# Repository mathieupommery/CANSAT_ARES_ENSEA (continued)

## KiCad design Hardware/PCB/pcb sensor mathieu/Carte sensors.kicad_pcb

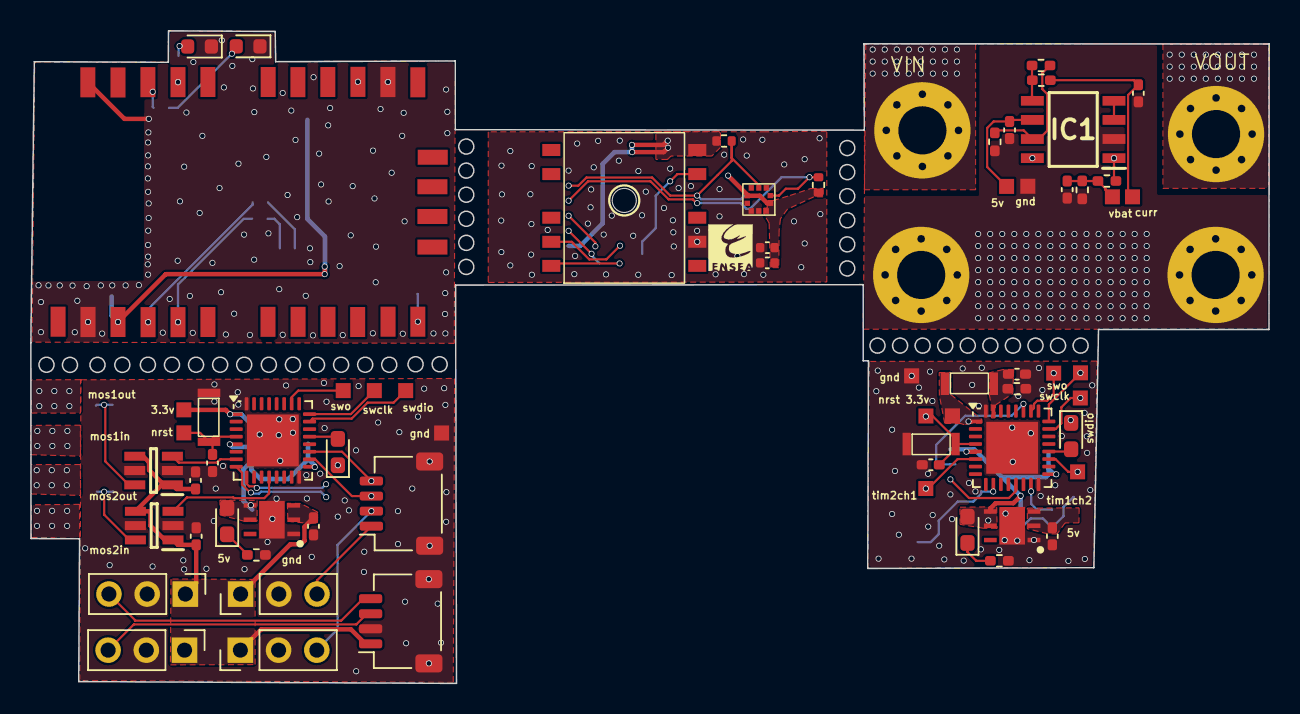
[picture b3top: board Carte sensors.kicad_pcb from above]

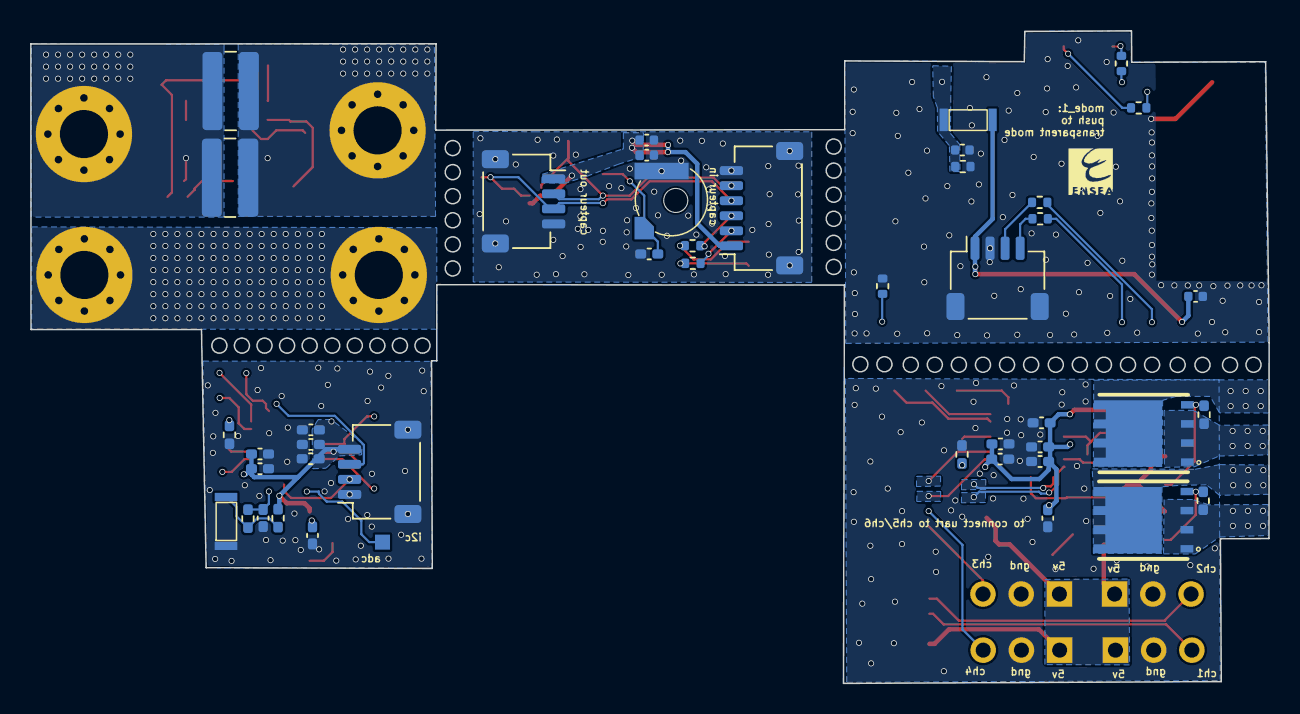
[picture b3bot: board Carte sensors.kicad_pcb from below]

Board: 2 copper layers, 82.3 x 43.4 mm, 94 parts (43 on the bottom side), 59 nets.

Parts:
BT1: ML414S; MS421R-IV03E
C1: 10n; C_0402_1005Metric
C2, C3, C4: 100u; C_0402_1005Metric
C5: 4.7u; C_0402_1005Metric
C6: 100n; C_0402_1005Metric
C7, C16, C19, C23, C29: 10n; C_0402_1005Metric_Pad0.74x0.62mm_HandSolder
C8, C10, C12, C17, C24, C25, C26, C27, C28, C30: 1u; C_0402_1005Metric_Pad0.74x0.62mm_HandSolder
C9, C14, C15, C21, C22: 100n; C_0402_1005Metric_Pad0.74x0.62mm_HandSolder
C11, C18: 0.1u; C_0402_1005Metric_Pad0.74x0.62mm_HandSolder
C13, C20: 4.7u; C_0402_1005Metric_Pad0.74x0.62mm_HandSolder
D1, D2: LED_Small; LED_0603_1608Metric
D3, D4, D5, D6: LED; LED_0603_1608Metric_Pad1.05x0.95mm_HandSolder
H1, H2, H3, H4: MountingHole_Pad; MountingHole_3.2mm_M3_Pad_Via
IC1: TSC102IDT; SOIC127P600X175-8N
IC2, IC3: LDO40LPU33RY; SON95P300X300X90-7N-D
IC4, IC5: MCP14A0151T-E_CH; SOT95P270X145-6N
J1, J3, J4, J5, J6: Conn_01x04_Pin; JST_SH_SM04B-SRSS-TB_1x04-1MP_P1.00mm_Horizontal
J2: Conn_01x06; JST_SH_SM06B-SRSS-TB_1x06-1MP_P1.00mm_Horizontal
J7, J8, J9, J10: Conn_01x03_Pin; PinHeader_1x03_P2.54mm_Vertical
PA1010D1: PA1010D
Q1, Q2: BSC0909NS; PG-TDSON-8-5
R1, R2, R6: 220; R_0402_1005Metric
R3, R4, R17, R18: 1k; R_0402_1005Metric
R5: 10k; R_0402_1005Metric
R7, R8: 2.2k; R_0402_1005Metric
R9: 100R; R_0402_1005Metric_Pad0.72x0.64mm_HandSolder
R10, R15: 10m; R_1020_2550Metric_Pad1.33x5.20mm_HandSolder
R11: 2k; R_0402_1005Metric_Pad0.72x0.64mm_HandSolder
R12: 1k; R_0402_1005Metric_Pad0.72x0.64mm_HandSolder
R13: 20k; R_0402_1005Metric_Pad0.72x0.64mm_HandSolder
R14, R21, R23, R26: 10k; R_0402_1005Metric_Pad0.72x0.64mm_HandSolder
R16, R19, R24, R25: 80R; R_0402_1005Metric_Pad0.72x0.64mm_HandSolder
R20, R22: 40k; R_0402_1005Metric_Pad0.72x0.64mm_HandSolder
SW1: SW_Push; SW_KXT3
SW2: Boutton 2; SW_KXT3
SW3, SW5: RSTBTN; SW_KXT3
SW4: boot; SW_KXT3
Tarvos1: Tarvos III
U1, U2: STM32L432KCUx; QFN-32-1EP_5x5mm_P0.5mm_EP3.45x3.45mm
WSEN-PADS1: WSEN-PADS

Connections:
+5V: C8.1, C12.1, C25.2, C27.2, C30.1, IC1.6 (VCC), IC2.2 (EN), IC2.3 (VIN), IC3.2 (EN), IC3.3 (VIN), IC4.1 (VDD), IC4.4 (EN), IC5.1 (VDD), IC5.4 (EN), J5.1, J7.1, J8.1, J9.1, J10.1
ADC1_IN2_CURR: C7.2, R9.1
ADC1_IN3_VBAT: C9.2, R13.1, R14.2
ADC1_IN9: U1.10 (PA4), U2.10 (PA4)
ADC1_IN10: U1.11 (PA5), U2.11 (PA5)
B2: C29.1, R26.2, U2.15 (PB1)
BAT+: H2.1, IC1.8 (VP), R10.2, R15.2
CH1: J5.3, J7.3
CH2: J5.4, J8.3
CH3: J6.1, J9.3
CH4: J6.2, J10.3
CH5: J6.3, U1.18 (PA8)
CH6: J6.4, U1.19 (PA9)
GND: BT1.2 (-), C1.2, C2.2, C3.2, C4.2, C5.1, C6.1, C7.1, C8.2, C9.1, C10.2, C11.1, C12.2, C13.1, C14.1, C15.1, C16.1, C17.1, C18.1, C19.1, C20.1, C21.1, C22.1, C23.1, C24.1, C25.1, C26.2, C27.1, C28.2, C29.2, C30.2, D1.1 (K), D2.1 (K), H3.1, H4.1, IC1.2 (GND), IC2.1 (GND), IC2.7 (EP), IC3.1 (GND), IC3.7 (EP), IC4.2 (AGND), IC4.5 (GND), IC5.2 (AGND), IC5.5 (GND), J1.2, J1.MP, J2.6, J2.MP, J3.4, J3.MP, J4.1, J4.MP, J5.2, J5.MP, J6.MP, J7.2, J8.2, J9.2, J10.2, PA1010D1.7 (GND), R5.1, R6.1, R12.1, R14.1, R16.1, R19.1, R21.2, R24.1, R25.1, SW2.1, SW3.1, SW5.1, Tarvos1.2 (GND), Tarvos1.14 (WAKE-UP), Tarvos1.23 (GND), U1.16 (VSS), U1.32 (VSS), U1.33 (VSS), U2.16 (VSS), U2.32 (VSS), U2.33 (VSS), WSEN-PADS1.3 (RSVD), WSEN-PADS1.8 (GND), WSEN-PADS1.9 (GND)
MOS1IN: Q2.1 (S_1), Q2.2 (S_2), Q2.3 (S_3), R20.1
MOS1OUT: Q2.5 (D_1), Q2.6 (D_2), Q2.7 (D_3), Q2.8 (D_4), Q2.9
MOS2IN: Q1.1 (S_1), Q1.2 (S_2), Q1.3 (S_3), R22.1
MOS2OUT: Q1.5 (D_1), Q1.6 (D_2), Q1.7 (D_3), Q1.8 (D_4), Q1.9
MOSFET1: IC4.3 (IN), U1.7 (PA1)
MOSFET2: IC5.3 (IN), U1.12 (PA6)
unnamed: BT1.1 (+), C10.1, PA1010D1.9 (VBACKUP)
unnamed: D1.2 (A), R1.2
unnamed: D2.2 (A), R2.2
unnamed: D3.1 (K), R24.2
unnamed: D4.1 (K), R25.2
unnamed: D5.2 (A), U1.21 (PA11)
unnamed: D5.1 (K), R16.2
unnamed: D6.2 (A), U2.20 (PA10)
unnamed: D6.1 (K), R19.2
unnamed: IC1.3 (A1), IC1.4 (A2)
unnamed: IC1.7 (A3), R11.1, R12.2
unnamed: IC1.5 (OUT), R9.2, R11.2
unnamed: IC4.6 (~OUT), Q2.4 (G), R20.2
unnamed: IC5.6 (~OUT), Q1.4 (G), R22.2
unnamed: PA1010D1.5 (RX), R18.2
unnamed: PA1010D1.4 (TX), R17.2
unnamed: R23.2, R26.1, SW2.2
unnamed: R6.2, Tarvos1.12 (BOOT)
unnamed: C1.1, R5.2, SW1.1, Tarvos1.15 (MODE_1)
unnamed: R2.1, Tarvos1.20 (RX_IND)
unnamed: R1.1, Tarvos1.21 (TX_IND)
unnamed: R4.2, Tarvos1.5 (URXD)
unnamed: R3.2, Tarvos1.4 (UTXD)
unnamed: C11.2, SW3.2, U1.4 (NRST)
unnamed: C18.2, SW5.2, U2.4 (NRST)
unnamed: C19.2, R21.1, SW4.1, U2.31 (PH3)
OLED_SCL: J4.2, U2.13 (PA7)
OLED_SDA: J4.3, U2.27 (PB4)
RX: J1.4, R4.1
RX_GPS: J2.2, R18.1
SCL_P: J2.4, J3.3, R7.1, WSEN-PADS1.2 (SCL)
SDA_P: J2.5, J3.2, R8.2, WSEN-PADS1.4 (SDA)
SWCLK: U1.24 (PA14), U2.24 (PA14)
SWDIO: U1.23 (PA13), U2.23 (PA13)
SWO: U1.26 (PB3), U2.26 (PB3)
TX: J1.3, R3.1
TX_GPS: J2.3, R17.1
VDD_IO: C2.1, C3.1, C4.1, C5.2, C6.2, C13.2, C14.2, C15.2, C16.2, C17.2, C20.2, C21.2, C22.2, C23.2, C24.2, C26.1, C28.1, D3.2 (A), D4.2 (A), IC2.4 (VOUT), IC2.5 (VSENSE), IC3.4 (VOUT), IC3.5 (VSENSE), J1.1, J2.1, J3.1, J4.4, PA1010D1.10 (VCC), R7.2, R8.1, R23.1, SW1.2, SW4.2, Tarvos1.3 (VCC), U1.1 (VDD), U1.5 (VDDA), U1.17 (VDD), U2.1 (VDD), U2.5 (VDDA), U2.17 (VDD), WSEN-PADS1.1 (VDD_IO), WSEN-PADS1.6 (CS), WSEN-PADS1.10 (VDD)
VIN: H1.1, IC1.1 (VM), R10.1, R13.2, R15.1

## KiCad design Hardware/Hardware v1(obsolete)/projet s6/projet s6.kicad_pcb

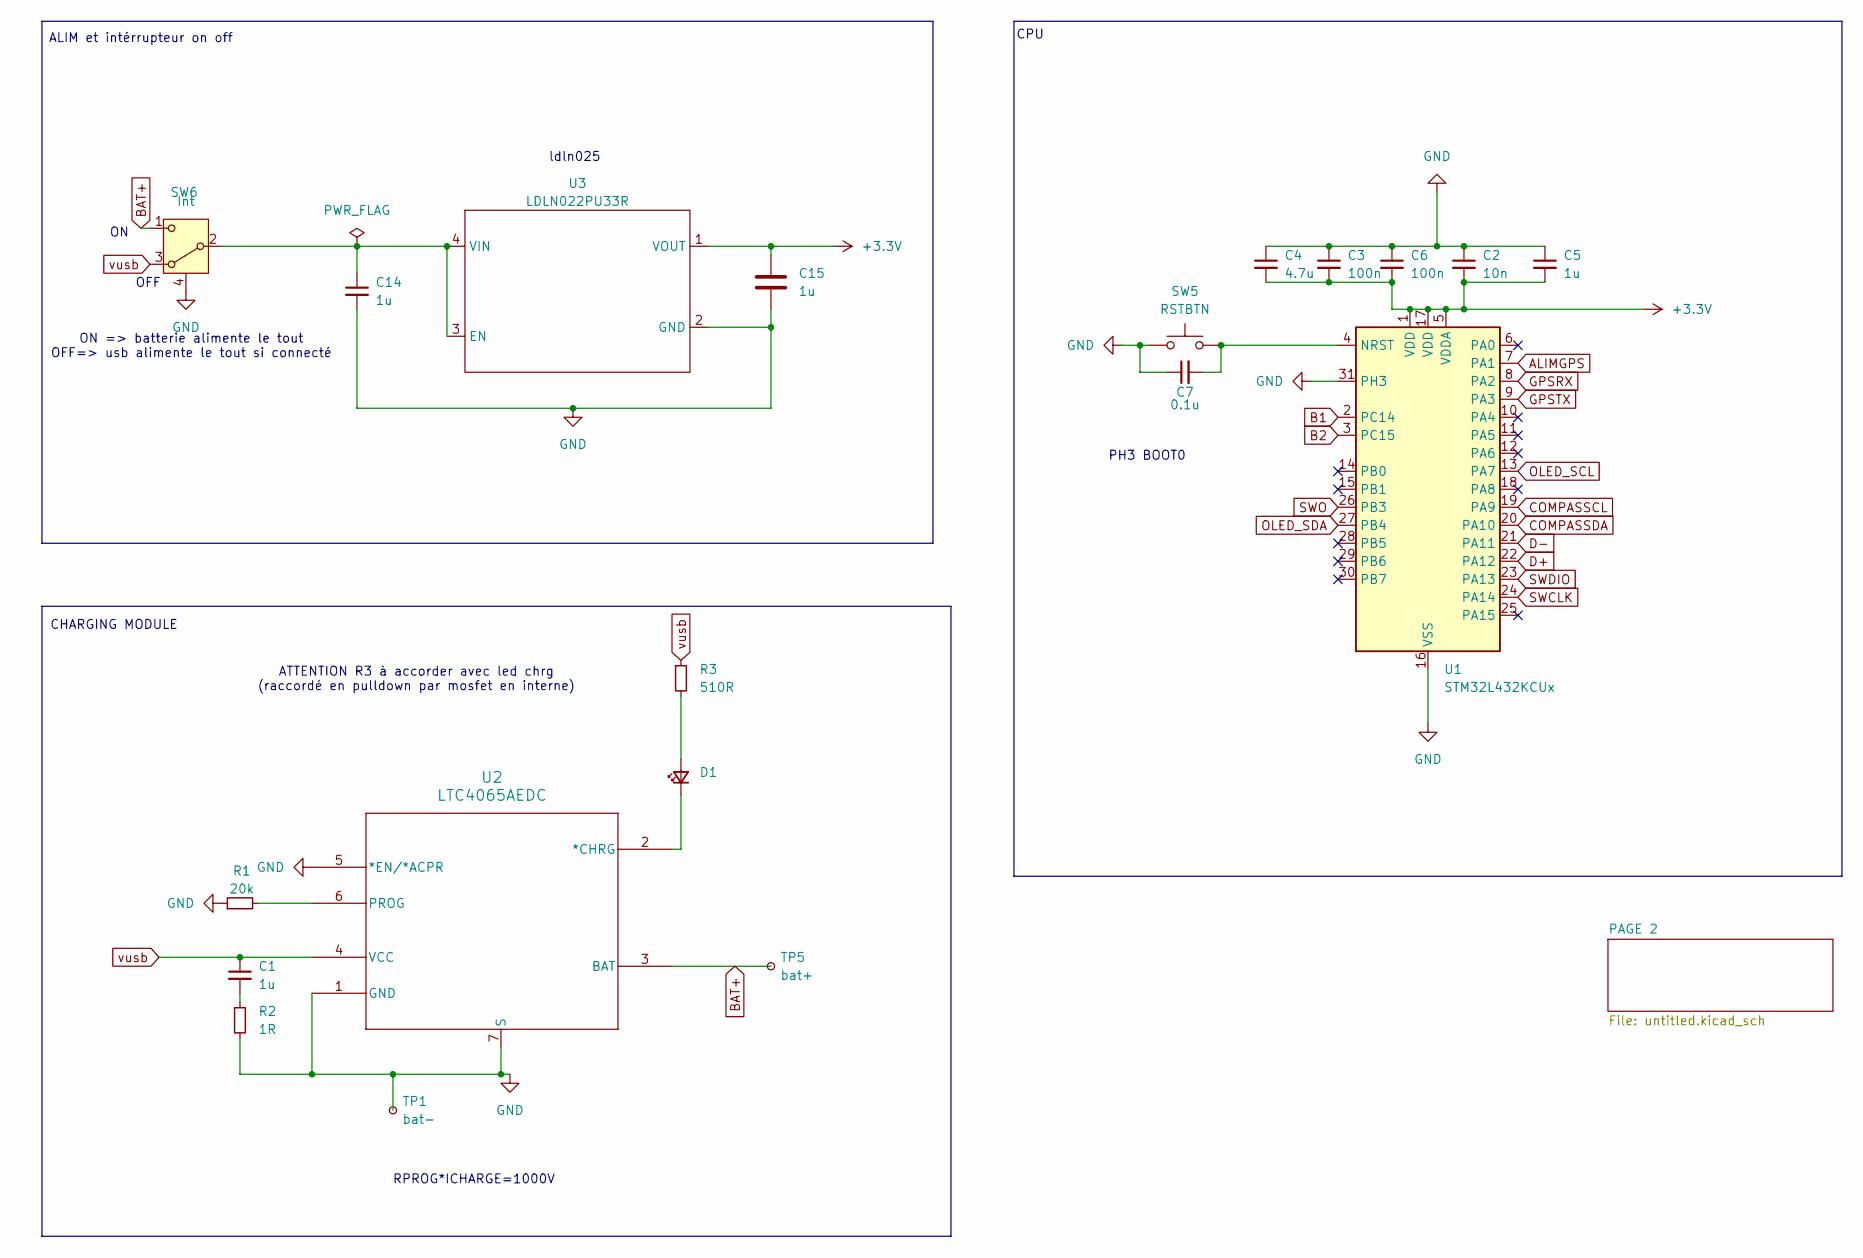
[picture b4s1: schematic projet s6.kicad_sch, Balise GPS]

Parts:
C1, C5, C14, C15: 1u; C_0402_1005Metric_Pad0.74x0.62mm_HandSolder
C2: 10n; C_0402_1005Metric_Pad0.74x0.62mm_HandSolder
C3, C6: 100n; C_0402_1005Metric_Pad0.74x0.62mm_HandSolder
C4: 4.7u; C_0402_1005Metric_Pad0.74x0.62mm_HandSolder
C7: 0.1u; C_0402_1005Metric_Pad0.74x0.62mm_HandSolder
D1: LED_0201_0603Metric_Pad0.64x0.40mm_HandSolder
R1: 20k; R_0402_1005Metric_Pad0.72x0.64mm_HandSolder
R2: 1R; R_0402_1005Metric_Pad0.72x0.64mm_HandSolder
R3: 510R; R_0402_1005Metric_Pad0.72x0.64mm_HandSolder
SW5: RSTBTN; SW_KXT3
SW6: Int; SW_PCM
TP1: bat-; TestPoint_THTPad_D1.0mm_Drill0.5mm
TP5: bat+; TestPoint_THTPad_D1.0mm_Drill0.5mm
U1: STM32L432KCUx; QFN-32-1EP_5x5mm_P0.5mm_EP3.45x3.45mm
U2: LTC4065AEDC; DFN-6_DC_LIT
U3: LDLN022PU33R; LDLN025PU33R

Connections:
+3.3V: C2.2, C3.2, C4.2, C5.2, C6.2, C15.1, U1.1 (VDD), U1.5 (VDDA), U1.17 (VDD), U3.1 (VOUT); also elsewhere on the board
ALIMGPS: U1.7 (PA1); also elsewhere on the board
B1: U1.2 (PC14); also elsewhere on the board
B2: U1.3 (PC15); also elsewhere on the board
BAT+: SW6.1 (C), TP5.1, U2.3 (BAT)
COMPASSCL: U1.19 (PA9); also elsewhere on the board
COMPASSDA: U1.20 (PA10); also elsewhere on the board
D+: U1.22 (PA12); also elsewhere on the board
D-: U1.21 (PA11); also elsewhere on the board
GND: C2.1, C3.1, C4.1, C5.1, C6.1, C7.1, C14.2, C15.2, R1.1, R2.2, SW5.1, SW6.4 (S), TP1.1, U1.16 (VSS), U1.31 (PH3), U1.32 (VSS), U1.33 (VSS), U2.1 (GND), U2.5 (*EN/*ACPR), U2.7 (S), U3.2 (GND); also elsewhere on the board
GPSRX: U1.8 (PA2); also elsewhere on the board
GPSTX: U1.9 (PA3); also elsewhere on the board
unnamed: C1.2, R2.1
unnamed: D1.2 (A), R3.2
unnamed: D1.1 (K), U2.2 (*CHRG)
unnamed: C14.1, SW6.2 (B), U3.3 (EN), U3.4 (VIN)
unnamed: C7.2, SW5.2, U1.4 (NRST)
unnamed: R1.2, U2.6 (PROG)
OLED_SCL: U1.13 (PA7); also elsewhere on the board
OLED_SDA: U1.27 (PB4); also elsewhere on the board
SWCLK: U1.24 (PA14); also elsewhere on the board
SWDIO: U1.23 (PA13); also elsewhere on the board
SWO: U1.26 (PB3); also elsewhere on the board
vusb: C1.1, R3.1, SW6.3 (A), U2.4 (VCC); also elsewhere on the board

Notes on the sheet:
PH3 BOOT0
CHARGING MODULE
OFF
ON => batterie alimente le tout OFF=> usb alimente le tout si connecté
ATTENTION R3 à accorder avec led chrg (raccordé en pulldown par mosfet en interne)
ldln025
ALIM et intérrupteur on off
RPROG*ICHARGE=1000V
CPU

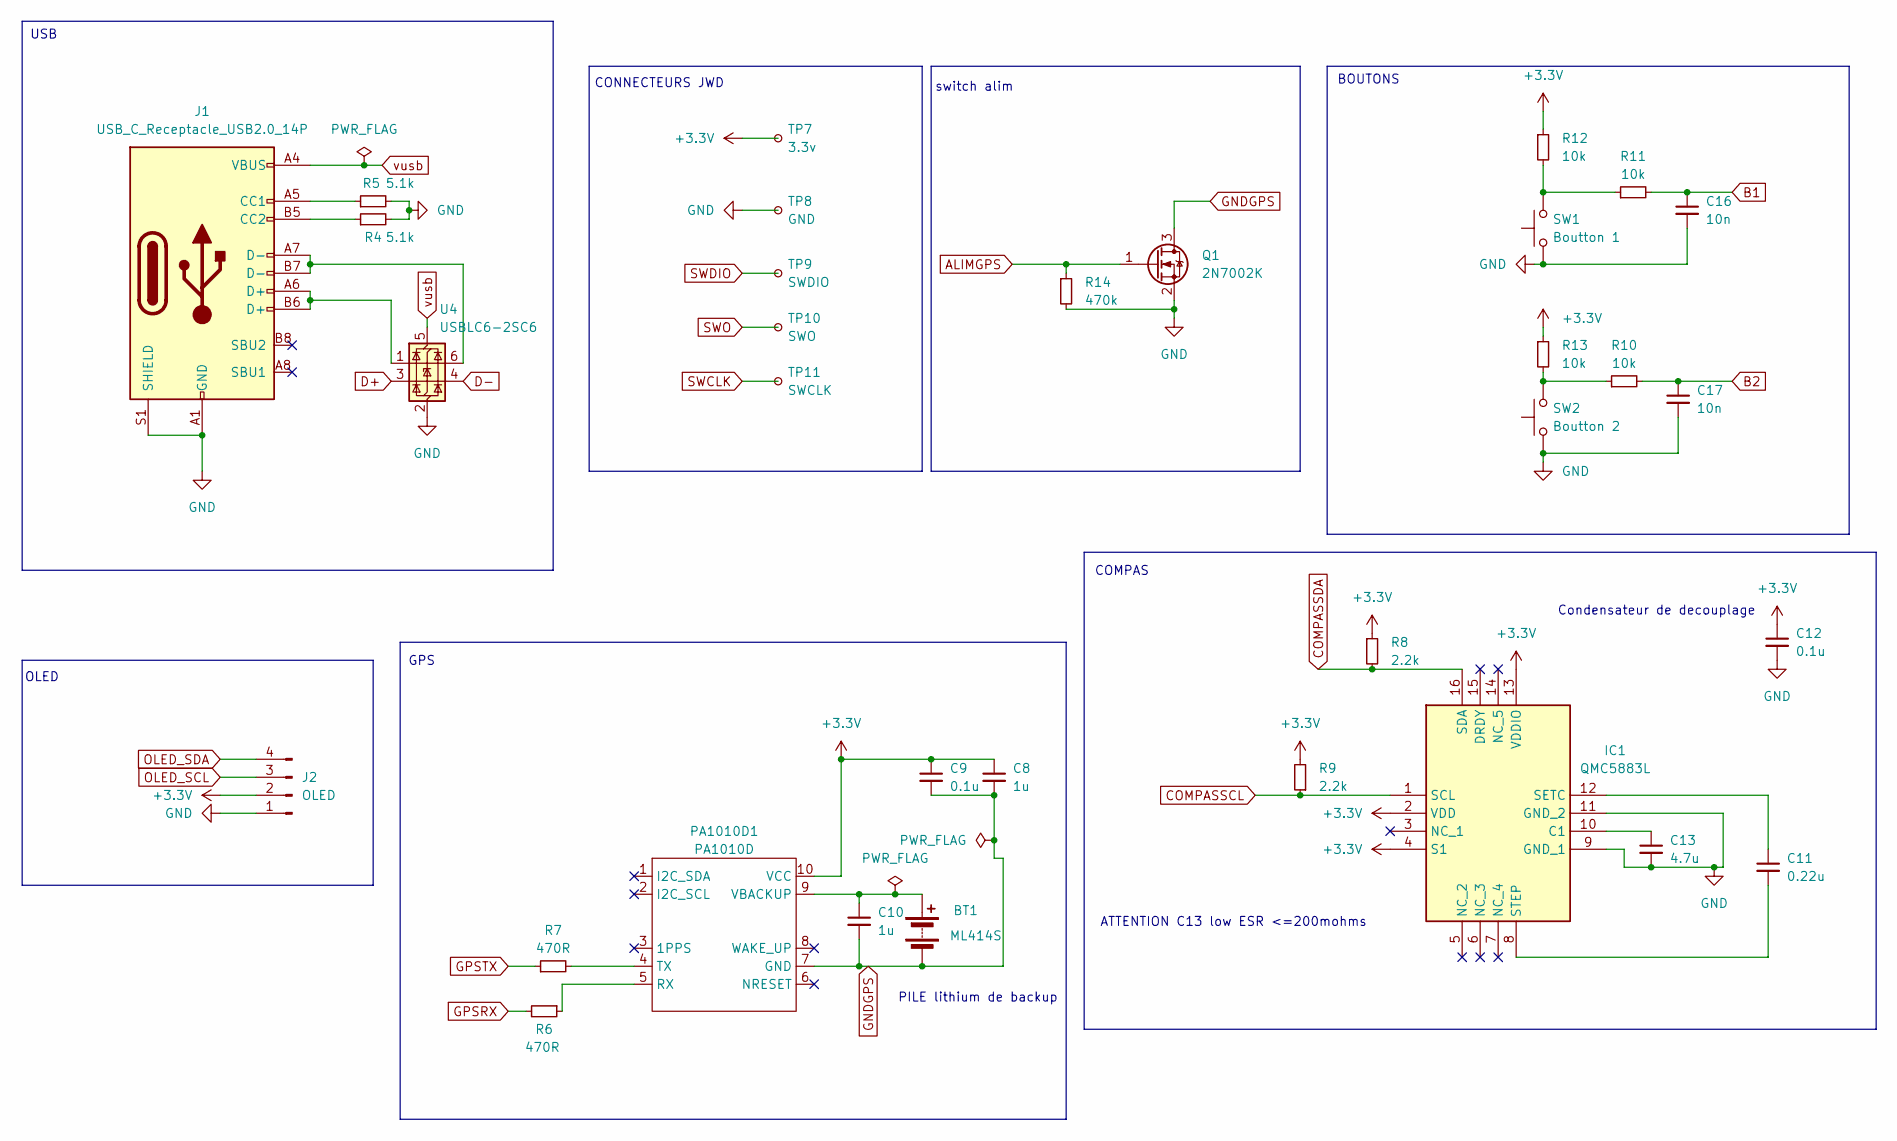
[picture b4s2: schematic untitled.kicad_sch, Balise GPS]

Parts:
BT1: ML414S; MS421R-IV03E
C8, C10: 1u; C_0402_1005Metric_Pad0.74x0.62mm_HandSolder
C9, C12: 0.1u; C_0402_1005Metric_Pad0.74x0.62mm_HandSolder
C11: 0.22u; C_0402_1005Metric_Pad0.74x0.62mm_HandSolder
C13: 4.7u; C_0603_1608Metric_Pad1.08x0.95mm_HandSolder
C16, C17: 10n; C_0402_1005Metric_Pad0.74x0.62mm_HandSolder
IC1: QMC5883L; Manufacturer_Part_Number QMC5883L
J1: USB_C_Receptacle_USB2.0_14P; USB4110_USBC_SMT
J2: OLED; PinSocket_1x04_P2.54mm_Vertical
PA1010D1: PA1010D
Q1: 2N7002K; 2N7002KQB
R4, R5: 5.1k; R_0402_1005Metric_Pad0.72x0.64mm_HandSolder
R6, R7: 470R; R_0402_1005Metric_Pad0.72x0.64mm_HandSolder
R8, R9: 2.2k; R_0402_1005Metric_Pad0.72x0.64mm_HandSolder
R10, R11, R12, R13: 10k; R_0402_1005Metric_Pad0.72x0.64mm_HandSolder
R14: 470k; R_0402_1005Metric_Pad0.72x0.64mm_HandSolder
SW1: Boutton 1; SW_PTS840
SW2: Boutton 2; SW_PTS840
TP7: 3.3v; TestPoint_THTPad_D1.0mm_Drill0.5mm
TP8: GND; TestPoint_THTPad_D1.0mm_Drill0.5mm
TP9: SWDIO; TestPoint_THTPad_D1.0mm_Drill0.5mm
TP10: SWO; TestPoint_THTPad_D1.0mm_Drill0.5mm
TP11: SWCLK; TestPoint_THTPad_D1.0mm_Drill0.5mm
U4: USBLC6-2SC6; SOT-23-6

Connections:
+3.3V: C8.1, C9.1, C12.1, IC1.2 (VDD), IC1.4 (S1), IC1.13 (VDDIO), J2.2, PA1010D1.10 (VCC), R8.1, R9.2, R12.1, R13.1, TP7.1; also elsewhere on the board
ALIMGPS: Q1.1 (G), R14.1; also elsewhere on the board
B1: C16.1, R11.2; also elsewhere on the board
B2: C17.1, R10.2; also elsewhere on the board
COMPASSCL: IC1.1 (SCL), R9.1; also elsewhere on the board
COMPASSDA: IC1.16 (SDA), R8.2; also elsewhere on the board
D+: U4.3 (I/O2); also elsewhere on the board
D-: U4.4 (I/O2); also elsewhere on the board
GND: C12.2, C13.2, C16.2, C17.2, IC1.9 (GND_1), IC1.11 (GND_2), J1.A1 (GND), J1.S1 (SHIELD), J2.1, Q1.2 (S), R4.2, R5.2, R14.2, SW1.1, SW2.1, TP8.1, U4.2 (GND); also elsewhere on the board
GNDGPS: BT1.2 (-), C8.2, C9.2, C10.2, PA1010D1.7 (GND), Q1.3 (D)
GPSRX: R6.2; also elsewhere on the board
GPSTX: R7.1; also elsewhere on the board
unnamed: BT1.1 (+), C10.1, PA1010D1.9 (VBACKUP)
unnamed: C13.1, IC1.10 (C1)
unnamed: C11.1, IC1.12 (SETC)
unnamed: C11.2, IC1.8 (STEP)
unnamed: J1.A5 (CC1), R5.1
unnamed: J1.B5 (CC2), R4.1
unnamed: J1.A6 (D+), J1.B6 (D+), U4.1 (I/O1)
unnamed: J1.A7 (D-), J1.B7 (D-), U4.6 (I/O1)
unnamed: PA1010D1.5 (RX), R6.1
unnamed: PA1010D1.4 (TX), R7.2
unnamed: R10.1, R13.2, SW2.2
unnamed: R11.1, R12.2, SW1.2
OLED_SCL: J2.3; also elsewhere on the board
OLED_SDA: J2.4; also elsewhere on the board
SWCLK: TP11.1; also elsewhere on the board
SWDIO: TP9.1; also elsewhere on the board
SWO: TP10.1; also elsewhere on the board
vusb: J1.A4 (VBUS), U4.5 (VBUS); also elsewhere on the board

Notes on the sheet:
PILE lithium de backup
OLED
COMPAS
switch alim
Condensateur de decouplage
GPS
ATTENTION C13 low ESR <=200mohms
USB
BOUTONS
CONNECTEURS JWD

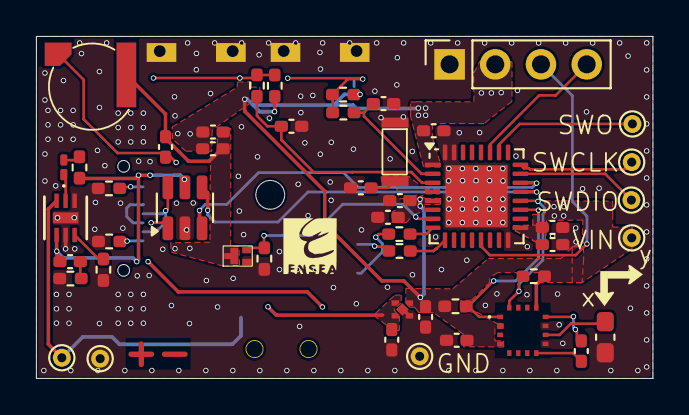
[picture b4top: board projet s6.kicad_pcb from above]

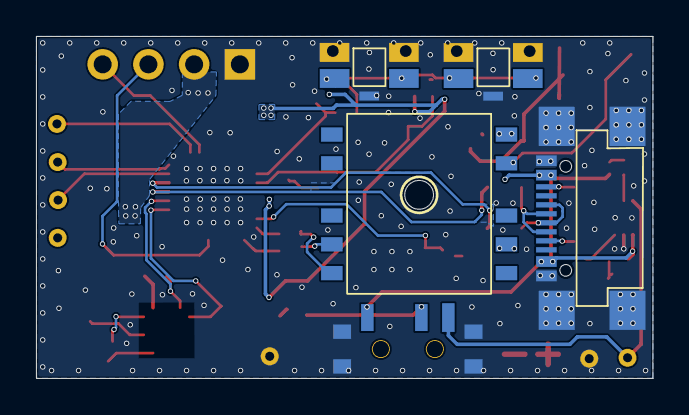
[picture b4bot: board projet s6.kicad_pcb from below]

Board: 2 copper layers, 34.2 x 19.0 mm, 53 parts (5 on the bottom side), 37 nets.

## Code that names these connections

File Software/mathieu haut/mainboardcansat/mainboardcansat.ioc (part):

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Mcu.Name=STM32G431C(6-8-B)Ux
Mcu.Package=UFQFPN48
Mcu.UserName=STM32G431CBUx
PA0.Signal=GPXTI0
PA1.Mode=IN2-Single-Ended
PA1.Signal=ADC1_IN2
PA11.Mode=Device
PA11.Signal=USB_DM
PA12.Mode=Device
PA12.Signal=USB_DP
PA13.Mode=Trace_Asynchronous_SW
PA13.Signal=SYS_JTMS-SWDIO
PA14.Mode=Trace_Asynchronous_SW
PA14.Signal=SYS_JTCK-SWCLK
PA15.Mode=I2C
PA15.Signal=I2C1_SCL
PA2.Mode=IN3-Single-Ended
PA2.Signal=ADC1_IN3
PA3.Signal=S_TIM2_CH4
PA4.Mode=IN17-Single-Ended
PA4.Signal=ADC2_IN17
PA5.Mode=Full_Duplex_Master
PA5.Signal=SPI1_SCK
PA6.Mode=Full_Duplex_Master
PA6.Signal=SPI1_MISO
PA7.Mode=Full_Duplex_Master
PA7.Signal=SPI1_MOSI
PA8.Mode=I2C
PA8.Signal=I2C3_SCL
PB1.Signal=GPXTI1
PB10.Mode=Asynchronous
PB10.Signal=LPUART1_RX
PB11.Mode=Asynchronous
PB11.Signal=LPUART1_TX
PB14.Signal=GPIO_Output
PB15.Signal=GPIO_Output
PB2.Signal=GPXTI2
PB3.Mode=Trace_Asynchronous_SW
PB3.Signal=SYS_JTDO-SWO
PB6.Mode=Asynchronous
PB6.Signal=USART1_TX
PB7.Mode=Asynchronous
PB7.Signal=USART1_RX
PB9.Mode=I2C
PB9.Signal=I2C1_SDA
PC11.Mode=I2C
PC11.Signal=I2C3_SDA
PC4.Signal=GPIO_Output
PC6.Signal=S_TIM3_CH1
PF0-OSC_IN.Mode=HSE-External-Oscillator
PF0-OSC_IN.Signal=RCC_OSC_IN
PF1-OSC_OUT.Mode=HSE-External-Oscillator
PF1-OSC_OUT.Signal=RCC_OSC_OUT
RCC.HSE_VALUE=16000000
RCC.SYSCLKFreq_VALUE=64000000
RCC.SYSCLKSource=RCC_SYSCLKSOURCE_PLLCLK
board=custom

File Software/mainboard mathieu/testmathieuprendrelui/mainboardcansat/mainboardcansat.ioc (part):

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Mcu.Name=STM32G431C(6-8-B)Ux
Mcu.Package=UFQFPN48
Mcu.UserName=STM32G431CBUx
PA1.Mode=IN2-Single-Ended
PA1.Signal=ADC1_IN2
PA11.Mode=Device
PA11.Signal=USB_DM
PA12.Mode=Device
PA12.Signal=USB_DP
PA13.Mode=Trace_Asynchronous_SW
PA13.Signal=SYS_JTMS-SWDIO
PA14.Mode=Trace_Asynchronous_SW
PA14.Signal=SYS_JTCK-SWCLK
PA15.Mode=I2C
PA15.Signal=I2C1_SCL
PA2.Mode=IN3-Single-Ended
PA2.Signal=ADC1_IN3
PA3.Mode=Asynchronous
PA3.Signal=LPUART1_RX
PA4.Mode=IN17-Single-Ended
PA4.Signal=ADC2_IN17
PA5.Mode=Full_Duplex_Master
PA5.Signal=SPI1_SCK
PA6.Mode=Full_Duplex_Master
PA6.Signal=SPI1_MISO
PA7.Mode=Full_Duplex_Master
PA7.Signal=SPI1_MOSI
PA8.Mode=I2C
PA8.Signal=I2C3_SCL
PB1.Signal=GPXTI1
PB11.Mode=Asynchronous
PB11.Signal=LPUART1_TX
PB14.Signal=GPIO_Output
PB15.Signal=GPIO_Output
PB2.Signal=GPXTI2
PB3.Mode=Trace_Asynchronous_SW
PB3.Signal=SYS_JTDO-SWO
PB5.GPIOParameters=GPIO_Label
PB5.GPIO_Label=BAROEXTI
PB5.Signal=GPXTI5
PB6.Mode=Asynchronous
PB6.Signal=USART1_TX
PB7.Mode=Asynchronous
PB7.Signal=USART1_RX
PB9.Mode=I2C
PB9.Signal=I2C1_SDA
PC11.Mode=I2C
PC11.Signal=I2C3_SDA
PC4.Signal=GPIO_Output
PC6.Signal=S_TIM3_CH1
PF0-OSC_IN.Mode=HSE-External-Oscillator
PF0-OSC_IN.Signal=RCC_OSC_IN
PF1-OSC_OUT.Mode=HSE-External-Oscillator
PF1-OSC_OUT.Signal=RCC_OSC_OUT
RCC.HSE_VALUE=16000000
RCC.SYSCLKFreq_VALUE=64000000
RCC.SYSCLKSource=RCC_SYSCLKSOURCE_PLLCLK
board=custom

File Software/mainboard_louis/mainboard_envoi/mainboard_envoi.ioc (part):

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Mcu.Name=STM32G431C(6-8-B)Ux
Mcu.Package=UFQFPN48
Mcu.UserName=STM32G431CBUx
PA1.Mode=IN2-Single-Ended
PA1.Signal=ADC1_IN2
PA11.Mode=Device
PA11.Signal=USB_DM
PA12.Mode=Device
PA12.Signal=USB_DP
PA13.Mode=Trace_Asynchronous_SW
PA13.Signal=SYS_JTMS-SWDIO
PA14.Mode=Trace_Asynchronous_SW
PA14.Signal=SYS_JTCK-SWCLK
PA2.Mode=IN3-Single-Ended
PA2.Signal=ADC1_IN3
PA3.Mode=Asynchronous
PA3.Signal=LPUART1_RX
PA4.Mode=IN17-Single-Ended
PA4.Signal=ADC2_IN17
PA5.Mode=Full_Duplex_Master
PA5.Signal=SPI1_SCK
PA6.Mode=Full_Duplex_Master
PA6.Signal=SPI1_MISO
PA7.Mode=Full_Duplex_Master
PA7.Signal=SPI1_MOSI
PA8.Mode=I2C
PA8.Signal=I2C3_SCL
PB1.Signal=GPXTI1
PB11.Mode=Asynchronous
PB11.Signal=LPUART1_TX
PB14.Signal=GPIO_Output
PB15.Signal=GPIO_Output
PB2.Signal=GPXTI2
PB3.Mode=Trace_Asynchronous_SW
PB3.Signal=SYS_JTDO-SWO
PB6.GPIOParameters=GPIO_Label
PB6.GPIO_Label=USART1_TX_GPS
PB6.Mode=Asynchronous
PB6.Signal=USART1_TX
PB7.GPIOParameters=GPIO_Label
PB7.GPIO_Label=USART1_RX_GPS
PB7.Mode=Asynchronous
PB7.Signal=USART1_RX
PC11.Mode=I2C
PC11.Signal=I2C3_SDA
PC4.Signal=GPIO_Output
PC6.Signal=S_TIM3_CH1
PF0-OSC_IN.Mode=HSE-External-Oscillator
PF0-OSC_IN.Signal=RCC_OSC_IN
PF1-OSC_OUT.Mode=HSE-External-Oscillator
PF1-OSC_OUT.Signal=RCC_OSC_OUT
RCC.HSE_VALUE=16000000
RCC.SYSCLKFreq_VALUE=90000000
RCC.SYSCLKSource=RCC_SYSCLKSOURCE_PLLCLK
board=custom

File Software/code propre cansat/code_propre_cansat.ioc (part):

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Mcu.Name=STM32G431C(6-8-B)Ux
Mcu.Package=UFQFPN48
Mcu.UserName=STM32G431CBUx
PA1.Signal=S_TIM2_CH2
PA13.Mode=Trace_Asynchronous_SW
PA13.Signal=SYS_JTMS-SWDIO
PA14.Mode=Trace_Asynchronous_SW
PA14.Signal=SYS_JTCK-SWCLK
PA15.Mode=I2C
PA15.Signal=I2C1_SCL
PA2.Mode=IN3-Single-Ended
PA2.Signal=ADC1_IN3
PA3.Mode=Asynchronous
PA3.Signal=LPUART1_RX
PA4.GPIOParameters=GPIO_ModeDefaultEXTI
PA4.GPIO_ModeDefaultEXTI=GPIO_MODE_IT_RISING_FALLING
PA4.Signal=GPXTI4
PA8.Mode=I2C
PA8.Signal=I2C3_SCL
PB1.GPIOParameters=GPIO_PuPd,GPIO_ModeDefaultEXTI
PB1.GPIO_ModeDefaultEXTI=GPIO_MODE_IT_RISING
PB1.GPIO_PuPd=GPIO_NOPULL
PB1.Signal=GPXTI1
PB11.Mode=Asynchronous
PB11.Signal=LPUART1_TX
PB14.GPIOParameters=GPIO_Label
PB14.GPIO_Label=LED_ROUGE
PB14.Signal=GPIO_Output
PB15.GPIOParameters=GPIO_Label
PB15.GPIO_Label=PWEN
PB15.Signal=GPIO_Output
PB2.GPIOParameters=GPIO_Label
PB2.GPIO_Label=SDDETECT
PB2.Signal=GPXTI2
PB3.Mode=Trace_Asynchronous_SW
PB3.Signal=SYS_JTDO-SWO
PB6.Mode=Asynchronous
PB6.Signal=USART1_TX
PB7.Mode=Asynchronous
PB7.Signal=USART1_RX
PB9.Mode=I2C
PB9.Signal=I2C1_SDA
PC11.Mode=I2C
PC11.Signal=I2C3_SDA
PC6.Signal=S_TIM3_CH1
PF0-OSC_IN.Mode=HSE-External-Oscillator
PF0-OSC_IN.Signal=RCC_OSC_IN
PF1-OSC_OUT.Mode=HSE-External-Oscillator
PF1-OSC_OUT.Signal=RCC_OSC_OUT
RCC.HSE_VALUE=16000000
RCC.SYSCLKFreq_VALUE=100000000
RCC.SYSCLKSource=RCC_SYSCLKSOURCE_PLLCLK
board=custom

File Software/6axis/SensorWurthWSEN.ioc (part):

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Mcu.Name=STM32L476R(C-E-G)Tx
Mcu.Package=LQFP64
Mcu.UserName=STM32L476RGTx
PA13\ (JTMS-SWDIO).GPIOParameters=GPIO_Label
PA13\ (JTMS-SWDIO).GPIO_Label=TMS
PA13\ (JTMS-SWDIO).Mode=Serial_Wire
PA13\ (JTMS-SWDIO).Signal=SYS_JTMS-SWDIO
PA14\ (JTCK-SWCLK).GPIOParameters=GPIO_Label
PA14\ (JTCK-SWCLK).GPIO_Label=TCK
PA14\ (JTCK-SWCLK).Mode=Serial_Wire
PA14\ (JTCK-SWCLK).Signal=SYS_JTCK-SWCLK
PA2.GPIOParameters=GPIO_Speed,GPIO_PuPd,GPIO_Label,GPIO_Mode
PA2.GPIO_Label=USART_TX
PA2.GPIO_Mode=GPIO_MODE_AF_PP
PA2.GPIO_PuPd=GPIO_NOPULL
PA2.GPIO_Speed=GPIO_SPEED_FREQ_VERY_HIGH
PA2.Mode=Asynchronous
PA2.Signal=USART2_TX
PA3.GPIOParameters=GPIO_Speed,GPIO_PuPd,GPIO_Label,GPIO_Mode
PA3.GPIO_Label=USART_RX
PA3.GPIO_Mode=GPIO_MODE_AF_PP
PA3.GPIO_PuPd=GPIO_NOPULL
PA3.GPIO_Speed=GPIO_SPEED_FREQ_VERY_HIGH
PA3.Mode=Asynchronous
PA3.Signal=USART2_RX
PA5.GPIOParameters=GPIO_Speed,GPIO_PuPd,GPIO_Label,GPIO_ModeDefaultOutputPP
PA5.GPIO_Label=LD2 [green Led]
PA5.GPIO_ModeDefaultOutputPP=GPIO_MODE_OUTPUT_PP
PA5.GPIO_PuPd=GPIO_NOPULL
PA5.GPIO_Speed=GPIO_SPEED_FREQ_LOW
PA5.Signal=GPIO_Output
PB3\ (JTDO-TRACESWO).GPIOParameters=GPIO_Label
PB3\ (JTDO-TRACESWO).GPIO_Label=SWO
PB3\ (JTDO-TRACESWO).Signal=SYS_JTDO-SWO
PB8.GPIOParameters=GPIO_Pu
PB8.GPIO_Pu=GPIO_PULLUP
PB8.Mode=I2C
PB8.Signal=I2C1_SCL
PB9.GPIOParameters=GPIO_Pu
PB9.GPIO_Pu=GPIO_PULLUP
PB9.Mode=I2C
PB9.Signal=I2C1_SDA
PC13.GPIOParameters=GPIO_PuPd,GPIO_Label,GPIO_ModeDefaultEXTI
PC13.GPIO_Label=B1 [Blue PushButton]
PC13.GPIO_ModeDefaultEXTI=GPIO_MODE_IT_FALLING
PC13.GPIO_PuPd=GPIO_NOPULL
PC13.Signal=GPXTI13
PC14-OSC32_IN\ (PC14).Mode=LSE-External-Oscillator
PC14-OSC32_IN\ (PC14).Signal=RCC_OSC32_IN
PC15-OSC32_OUT\ (PC15).Mode=LSE-External-Oscillator
PC15-OSC32_OUT\ (PC15).Signal=RCC_OSC32_OUT
PH0-OSC_IN\ (PH0).Signal=RCC_OSC_IN
PH1-OSC_OUT\ (PH1).Signal=RCC_OSC_OUT
RCC.HSE_VALUE=8000000
RCC.SYSCLKFreq_VALUE=80000000
RCC.SYSCLKSource=RCC_SYSCLKSOURCE_PLLCLK
board=NUCLEO-L476RG
boardIOC=true

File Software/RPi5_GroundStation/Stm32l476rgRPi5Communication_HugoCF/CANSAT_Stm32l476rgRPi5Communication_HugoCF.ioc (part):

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Mcu.Name=STM32L476R(C-E-G)Tx
Mcu.Package=LQFP64
Mcu.UserName=STM32L476RGTx
PA10.Mode=Asynchronous
PA10.Signal=USART1_RX
PA13\ (JTMS-SWDIO).GPIOParameters=GPIO_Label
PA13\ (JTMS-SWDIO).GPIO_Label=TMS
PA13\ (JTMS-SWDIO).Mode=Serial_Wire
PA13\ (JTMS-SWDIO).Signal=SYS_JTMS-SWDIO
PA14\ (JTCK-SWCLK).GPIOParameters=GPIO_Label
PA14\ (JTCK-SWCLK).GPIO_Label=TCK
PA14\ (JTCK-SWCLK).Mode=Serial_Wire
PA14\ (JTCK-SWCLK).Signal=SYS_JTCK-SWCLK
PA2.Mode=Asynchronous
PA2.Signal=USART2_TX
PA3.GPIOParameters=GPIO_Speed,GPIO_PuPd,GPIO_Label,GPIO_Mode
PA3.GPIO_Label=USART_RX
PA3.GPIO_Mode=GPIO_MODE_AF_PP
PA3.GPIO_PuPd=GPIO_NOPULL
PA3.GPIO_Speed=GPIO_SPEED_FREQ_VERY_HIGH
PA3.Mode=Asynchronous
PA3.Signal=USART2_RX
PA5.GPIOParameters=GPIO_Speed,GPIO_PuPd,GPIO_Label,GPIO_ModeDefaultOutputPP
PA5.GPIO_Label=LD2 [green Led]
PA5.GPIO_ModeDefaultOutputPP=GPIO_MODE_OUTPUT_PP
PA5.GPIO_PuPd=GPIO_NOPULL
PA5.GPIO_Speed=GPIO_SPEED_FREQ_LOW
PA5.Signal=GPIO_Output
PA9.Mode=Asynchronous
PA9.Signal=USART1_TX
PB3\ (JTDO-TRACESWO).GPIOParameters=GPIO_Label
PB3\ (JTDO-TRACESWO).GPIO_Label=SWO
PB3\ (JTDO-TRACESWO).Signal=SYS_JTDO-SWO
PC13.GPIOParameters=GPIO_PuPd,GPIO_Label,GPIO_ModeDefaultEXTI
PC13.GPIO_Label=B1 [Blue PushButton]
PC13.GPIO_ModeDefaultEXTI=GPIO_MODE_IT_FALLING
PC13.GPIO_PuPd=GPIO_NOPULL
PC13.Signal=GPXTI13
PC14-OSC32_IN\ (PC14).Mode=LSE-External-Oscillator
PC14-OSC32_IN\ (PC14).Signal=RCC_OSC32_IN
PC15-OSC32_OUT\ (PC15).Mode=LSE-External-Oscillator
PC15-OSC32_OUT\ (PC15).Signal=RCC_OSC32_OUT
PH0-OSC_IN\ (PH0).Signal=RCC_OSC_IN
PH1-OSC_OUT\ (PH1).Signal=RCC_OSC_OUT
RCC.HSE_VALUE=8000000
RCC.SYSCLKFreq_VALUE=80000000
RCC.SYSCLKSource=RCC_SYSCLKSOURCE_PLLCLK
board=NUCLEO-L476RG
boardIOC=true

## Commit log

2024-09-05 premiere udate
2024-09-17 debut github
2024-09-17 ytroeye
2024-09-17 mise a jour hugo
2024-09-17 Empty base
2024-09-29 regu
2024-09-29 empreinte
2024-09-29 librairie
2024-09-29 usb c wurth
2024-10-03 avancement du kicad
2024-10-06 fin pcb
2024-10-19 yoo2
2024-10-20 pcb v1 fini
2024-10-20 bom remplis
2024-10-20 PCB sensor
2024-10-20 Fichier 3D
2024-10-20 carte sensor
2024-10-20 nouvelle carte
2024-10-21 tarvos III
2024-10-22 pcb sensor fi,is
2024-10-22 finis
2024-10-22 MAJ séances
2024-10-22 final change pcb (on espere)
2024-10-22 tests
2024-10-22 modif
2024-10-23 carte mathieu
2024-10-27 Question
    Manque pas un 100nF au VDD_IO de l'accel ?
2024-10-27 ekip
2024-11-02 step
2024-11-02 pcb step
2024-11-05 seance 05/11
2024-11-05 05/11
2024-11-05 test
2024-11-05 code v1
2024-11-05 readme
2024-11-05 bon de commande
2024-11-11 schema readme
2024-11-11 re schema
2024-11-12 maj readme
2024-11-14 MAJ read.me
2024-11-26 Add of C code to generate UART buffers from STM32L476RG
2024-11-28 Impression 3D de la partie mécanique
2024-11-28 Photo
2024-11-29 Readme.md
2024-12-03 accent
2024-12-03 ajout simulation
2024-12-03 maj simulation
2024-12-03 testt
2024-12-08 debut code principal
2024-12-08 update tree
2024-12-08 code
2024-12-17 Create Code simulation du déploiement du parachute
2025-01-14 Ajout code 6axes
2025-01-21 ajout stationsol 3D
2025-01-21 modif init 6axis
2025-01-21 maj station
2025-01-21 Read me
2025-01-23 ajouts imgs
2025-01-24 modif simulations
2025-01-24 impression_3D_maj
2025-01-24 maj_soft_tarvos_sensor
2025-01-27 ajout diapo
2025-01-27 maj soft
2025-01-28 video
2025-01-31 modif readme
2025-01-31 ajout CM5 Pi
2025-02-02 imp video
2025-02-04 ajout stl station sol
2025-02-04 stl station sol
2025-02-08 travail
2025-02-08 stationsol
2025-02-08 servomoteur_ouv_ferm
2025-02-10 pcbv2
2025-02-11 Create parachute à acheter
    Les liens des parachutes que l'on pourrait acheter
2025-02-11 Update parachute à acheter
2025-02-11 servoend.c
2025-02-11 servoenda.h
2025-02-11 maj station sol
2025-02-13 flexpcb
2025-02-14 pcb panel
2025-03-12 maj 3D station sol
2025-03-13 programme mainboard
2025-03-18 adding of the ground station code
2025-03-18 adding of the C code for communication TarvosIII
2025-03-20 modif 3D
2025-03-20 maj 3D
2025-03-20 adding of the comm code
2025-03-20 dstore
2025-03-21 readme maj
2025-03-23 maj TarvosIII C code
2025-03-24 3D station sol
2025-03-25 vbfdj
2025-03-27 Rename mecanisme.GIF to Docs/IMG/mecanisme.GIF
2025-03-27 Rename test_bas.GIF to Docs/IMG/ test_bas.GIF
2025-03-27 Rename Conversion Successful.gif to lancement.gif
2025-03-27 rearangement de tous les pcb cree
2025-03-27 le github est pepite de chocolat
2025-04-01 mainboard v3
2025-04-22 Maj md + 3D station sol
2025-04-24 correction orthographe
2025-04-26 files rename
2025-04-26 maj software part
2025-05-01 adding of Cansat competition poster
2025-05-01 adding of CanSat poster
2025-06-14 update code
2025-06-29 last up
2025-07-01 updatemutexuart
2025-07-16 final update
2025-09-23 ADD VIDEO MECA
2025-09-23 Rename CANSAT2 v45.gif to CANSAT2_v45.gif
2025-09-23 Meca
